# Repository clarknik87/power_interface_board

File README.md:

View this project on [CADLAB.io](https://cadlab.io/project/23153). 

# power_interface_board

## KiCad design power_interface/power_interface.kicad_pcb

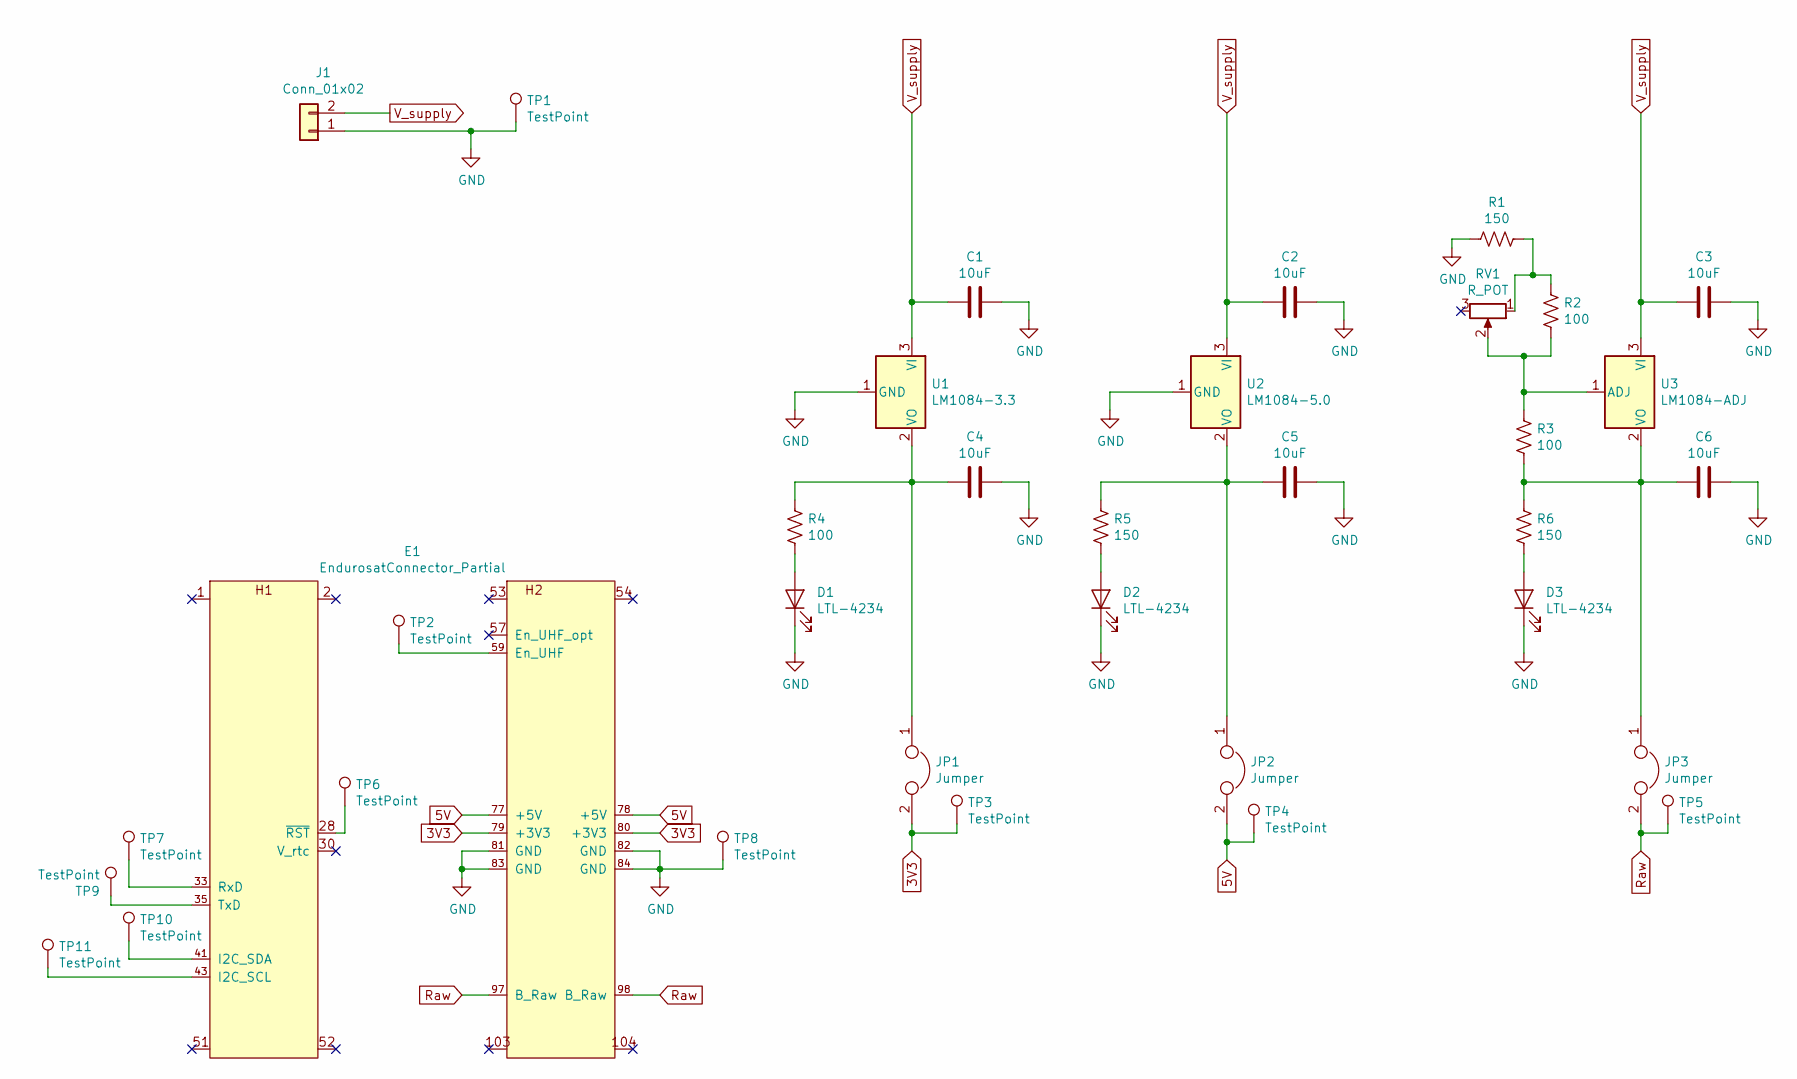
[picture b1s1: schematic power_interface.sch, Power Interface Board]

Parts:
C1, C2, C3, C4, C5, C6: 10uF; CP_Radial_Tantal_D5.0mm_P5.00mm
D1, D2, D3: LTL-4234; LED_D5.0mm
E1: EndurosatConnector_Partial; Endurosat_Connector_Partial_4x26_2.54mm
J1: Conn_01x02; Banana_Jack_2Pin
JP1, JP2, JP3: Jumper; PinHeader_1x02_P2.54mm_Vertical
R1, R5, R6: 150; R_Axial_DIN0207_L6.3mm_D2.5mm_P10.16mm_Horizontal
R2, R3, R4: 100; R_Axial_DIN0207_L6.3mm_D2.5mm_P10.16mm_Horizontal
RV1: R_POT; Potentiometer_Alps_RK09K_Single_Vertical
TP1, TP2, TP3, TP4, TP5, TP6, TP7, TP8, TP9, TP10, TP11: TestPoint; TestPoint_Keystone_5005-5009_Compact
U1: LM1084-3.3; TO-220-3_Horizontal_TabDown
U2: LM1084-5.0; TO-220-3_Horizontal_TabDown
U3: LM1084-ADJ; TO-220-3_Horizontal_TabDown

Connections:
3V3: E1.79 (+3V3), E1.80 (+3V3), JP1.2, TP3.1
5V: E1.77 (+5V), E1.78 (+5V), JP2.2, TP4.1
GND: C1.1, C2.1, C3.1, C4.1, C5.1, C6.1, D1.1 (K), D2.1 (K), D3.1 (K), E1.81 (GND), E1.82 (GND), E1.83 (GND), E1.84 (GND), J1.1, R1.2, TP1.1, TP8.1, U1.1 (GND), U2.1 (GND)
unnamed: C4.2, JP1.1, R4.1, U1.2 (VO)
unnamed: C5.2, JP2.1, R5.1, U2.2 (VO)
unnamed: C6.2, JP3.1, R3.2, R6.1, U3.2 (VO)
unnamed: D1.2 (A), R4.2
unnamed: D2.2 (A), R5.2
unnamed: D3.2 (A), R6.2
unnamed: E1.28 (~RST), TP6.1
unnamed: E1.33 (RxD), TP7.1
unnamed: E1.35 (TxD~), TP9.1
unnamed: E1.41 (I2C_SDA), TP10.1
unnamed: E1.43 (I2C_SCL), TP11.1
unnamed: E1.59 (En_UHF), TP2.1
unnamed: R1.1, R2.1, RV1.1
unnamed: R2.2, R3.1, RV1.2, U3.1 (ADJ)
Raw: E1.97 (B_Raw), E1.98 (B_Raw), JP3.2, TP5.1
V_supply: C1.2, C2.2, C3.2, J1.2, U1.3 (VI), U2.3 (VI), U3.3 (VI)

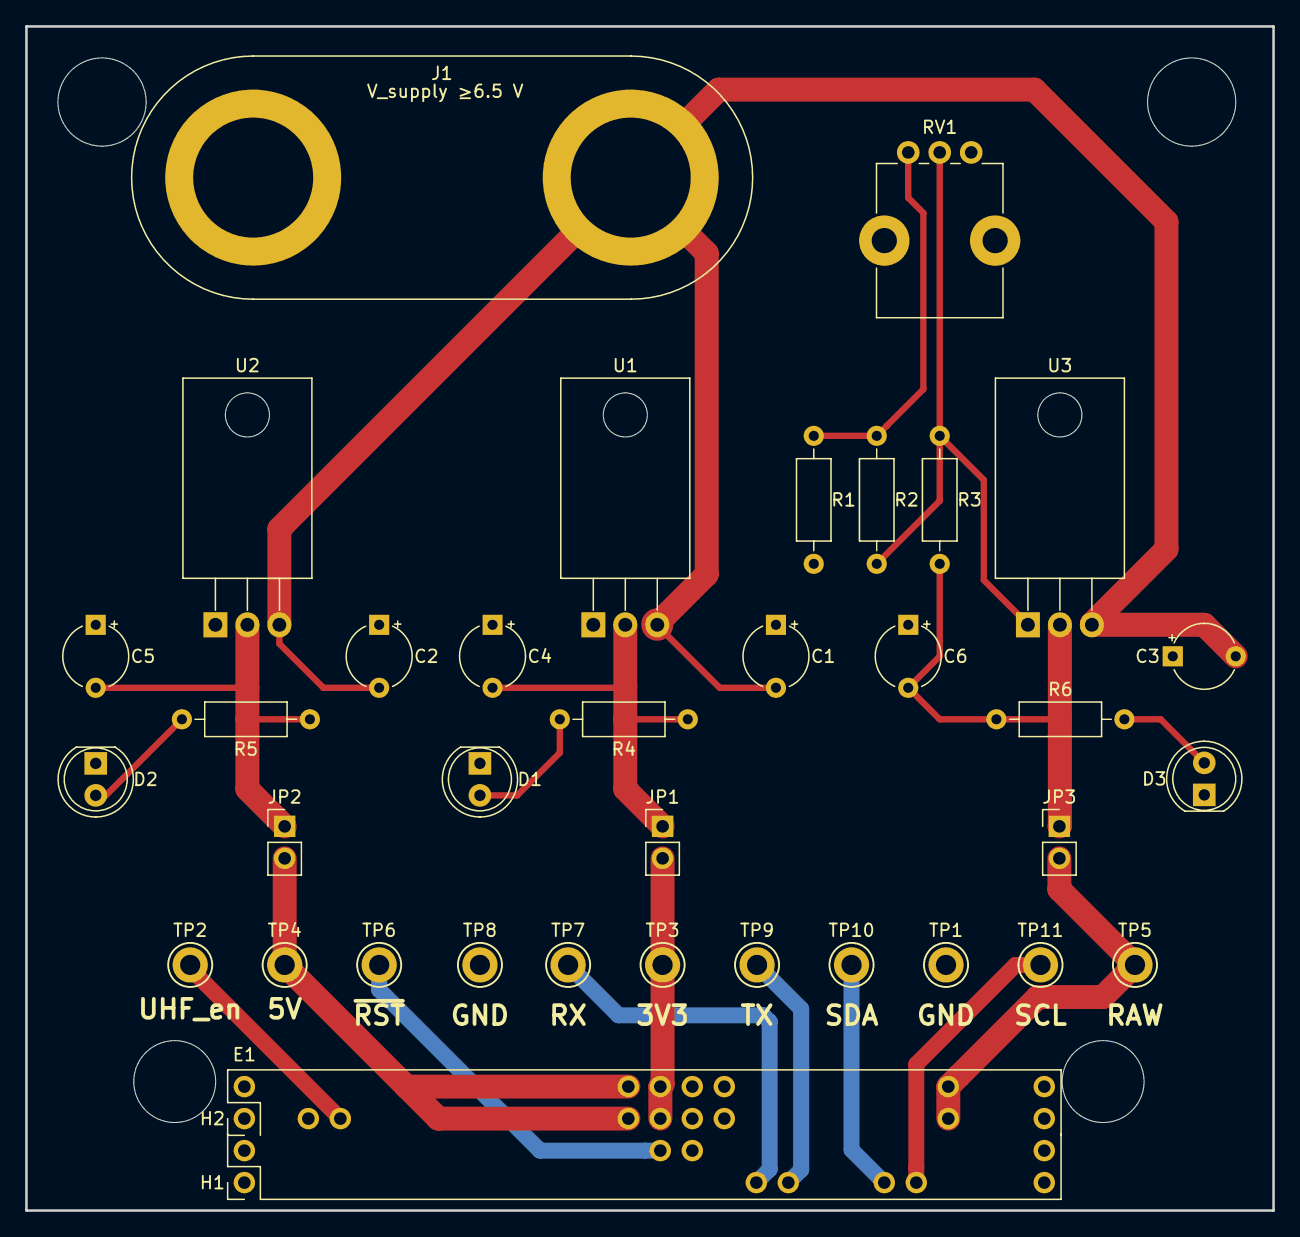
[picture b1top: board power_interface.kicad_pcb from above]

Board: 2 copper layers, 99.0 x 94.0 mm, 35 parts (0 on the bottom side), 19 nets.

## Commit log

2020-07-26 Power_interface board revision 1 completed. Current design is what is available in the drive, and is what will be ordered from JLCPCB
2020-07-26 Backlink to CADLAB.io has been added.
2020-07-28 Corrected a misplaced mounting hole. Verified connector layout against the computer board rev_14 layout
2020-07-28 added the zipped gerber file folder
